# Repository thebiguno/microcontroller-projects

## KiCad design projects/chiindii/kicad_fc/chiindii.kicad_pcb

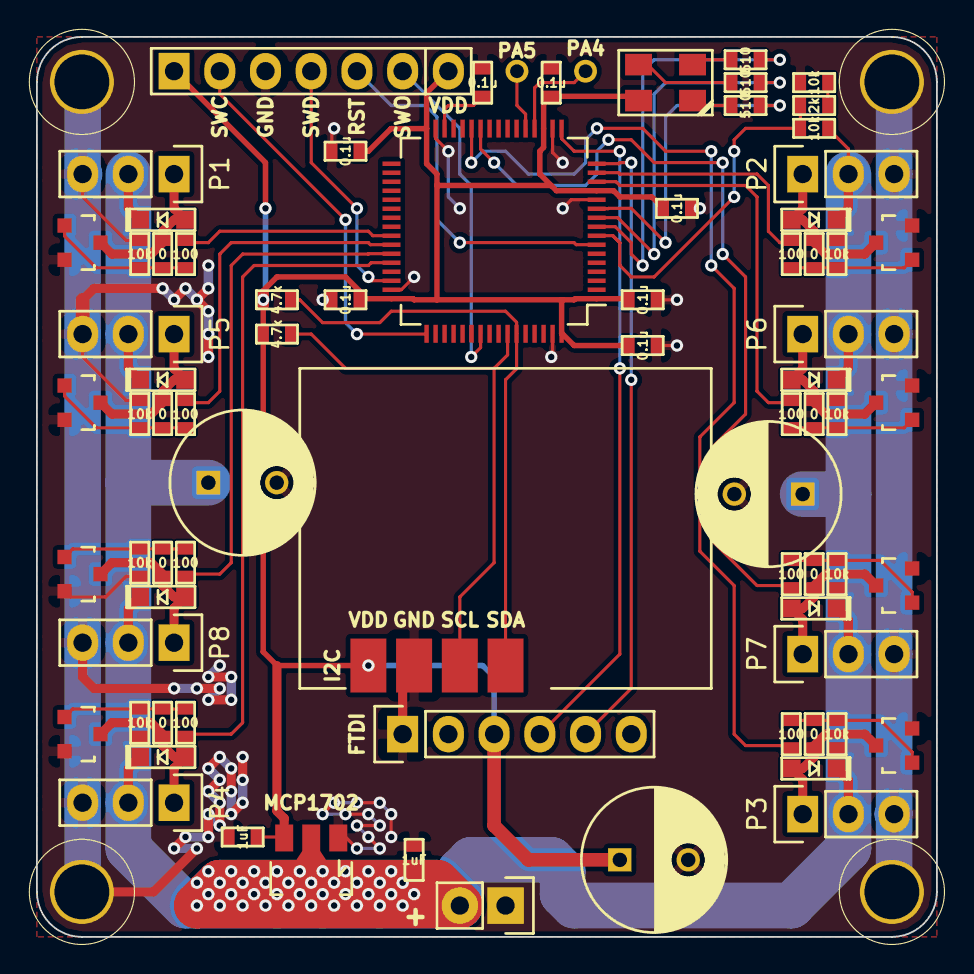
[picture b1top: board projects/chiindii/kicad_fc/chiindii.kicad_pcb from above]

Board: 2 copper layers, 50.0 x 50.0 mm, 81 parts (0 on the bottom side), 46 nets.

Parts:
C1, C2: 1uF; SM0603_VALUE
C3, C4, C11, C12, C13, C14, C15: 0.1u; SM0603_VALUE
C5, C6, C7: 470uF; C_Radial_D8_L13_P3.8
D1, D2, D3, D4, D5, D6, D7, D8: DSCHSMALL; SOD-323_DIODE
D10: RGB_LED_COMMON_ANODE_ALT1; LED_RGB_4-PLCC_ALT1
MP1, MP2, MP3, MP4: MOUNTING_HOLE; MOUNTING_HOLE_#4
P1, P2, P3, P4, P5, P6, P7, P8: CONN_01X03; Pin_Header_Straight_1x03
P9: STLINK; Pin_Header_Straight_1x07
P10: BATTERY; Pin_Header_Straight_1x02
P27: FTDI; Pin_Header_Straight_1x06
P33: I2C; Pin_Header_Straight_1x04
Q1, Q2, Q3, Q4, Q5, Q6, Q7, Q8: Q_NMOS_GSD; SOT-23
R1, R2, R7, R8, R13, R14, R34, R35: 100; SM0603_VALUE
R3, R6, R10, R12, R17, R18, R28, R33, R37, R39: 10k; SM0603_VALUE
R4, R5, R9, R11, R15, R32, R36, R38: 0; SM0603_VALUE
R16: 2k; SM0603_VALUE
R20, R21, R22: 510; SM0603_VALUE
R24, R27: 4.7k; SM0603_VALUE
U3: STM32F411; LQFP-64_10x10mm_Pitch0.5mm
VR1: MCP1702; SOT89-3_Housing
W1, W2: TEST_1P; Pin_Header_Straight_1x01

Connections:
+3V3: C2.1, C3.2, C5.1, C11.2, C12.2, C13.2, C14.2, C15.2, D10.1, P9.1, P9.7, P27.3, P33.1, R24.2, R27.2, U3.1, U3.13, U3.19, U3.32, U3.48, U3.64, VR1.3
+BATT: C1.1, C6.1, C7.1, D1.2, D2.2, D3.2, D4.2, D5.2, D6.2, D7.2, D8.2, P1.2, P2.2, P3.2, P4.2, P5.2, P6.2, P7.2, P8.2, P10.2, R18.2, VR1.2
/BATT_ADC: R16.2, R18.1, U3.8
/MOTOR1: R1.1, U3.41
/MOTOR2: R2.1, U3.15
/MOTOR3: R7.1, U3.27
/MOTOR4: R8.1, U3.44
/MOTOR5: R13.1, U3.42
/MOTOR6: R14.1, U3.14
/MOTOR7: R34.1, U3.26
/MOTOR8: R35.1, U3.43
/NRST: P9.5, U3.7
/PA4: U3.20, W2.1
/PA5: U3.21, W1.1
/RADIO_RX: P27.5, U3.16
/RADIO_TX: P27.4, U3.17
/SCL: P33.3, R24.1, U3.58
/SDA: P33.4, R27.1, U3.59
/SWCLK: P9.2, U3.49
/SWDIO: P9.4, U3.46
/SWO: P9.6, U3.55
GND: C1.2, C2.2, C3.1, C4.2, C5.2, C6.2, C7.2, C11.1, C12.1, C13.1, C14.1, C15.1, MP1.1, MP2.1, MP3.1, MP4.1, P1.3, P2.3, P3.3, P4.3, P5.3, P6.3, P7.3, P8.3, P9.3, P10.1, P27.1, P33.2, Q1.2, Q2.2, Q3.2, Q4.2, Q5.2, Q6.2, Q7.2, Q8.2, R3.1, R6.1, R10.1, R12.1, R17.1, R28.1, R33.1, R37.1, R39.1, U3.12, U3.18, U3.31, U3.47, U3.63, VR1.1
unnamed: C4.1, U3.30
unnamed: D1.1, P1.1, Q1.3, R4.2
unnamed: D2.1, P2.1, Q2.3, R5.2
unnamed: D3.1, P3.1, Q3.3, R9.2
unnamed: D4.1, P4.1, Q4.3, R11.2
unnamed: D5.1, P5.1, Q5.3, R15.2
unnamed: D6.1, P6.1, Q6.3, R32.2
unnamed: D7.1, P7.1, Q7.3, R36.2
unnamed: D8.1, P8.1, Q8.3, R38.2
unnamed: D10.2, R22.1
unnamed: D10.3, R21.1
unnamed: D10.4, R20.1
unnamed: Q1.1, R1.2, R3.2, R4.1
unnamed: Q2.1, R2.2, R5.1, R6.2
unnamed: Q3.1, R7.2, R9.1, R10.2
unnamed: Q4.1, R8.2, R11.1, R12.2
unnamed: Q5.1, R13.2, R15.1, R28.2
unnamed: Q6.1, R14.2, R32.1, R33.2
unnamed: Q7.1, R34.2, R36.1, R37.2
unnamed: Q8.1, R35.2, R38.1, R39.2
unnamed: R16.1, R17.2
unnamed: R20.2, U3.9
unnamed: R21.2, U3.10
unnamed: R22.2, U3.11

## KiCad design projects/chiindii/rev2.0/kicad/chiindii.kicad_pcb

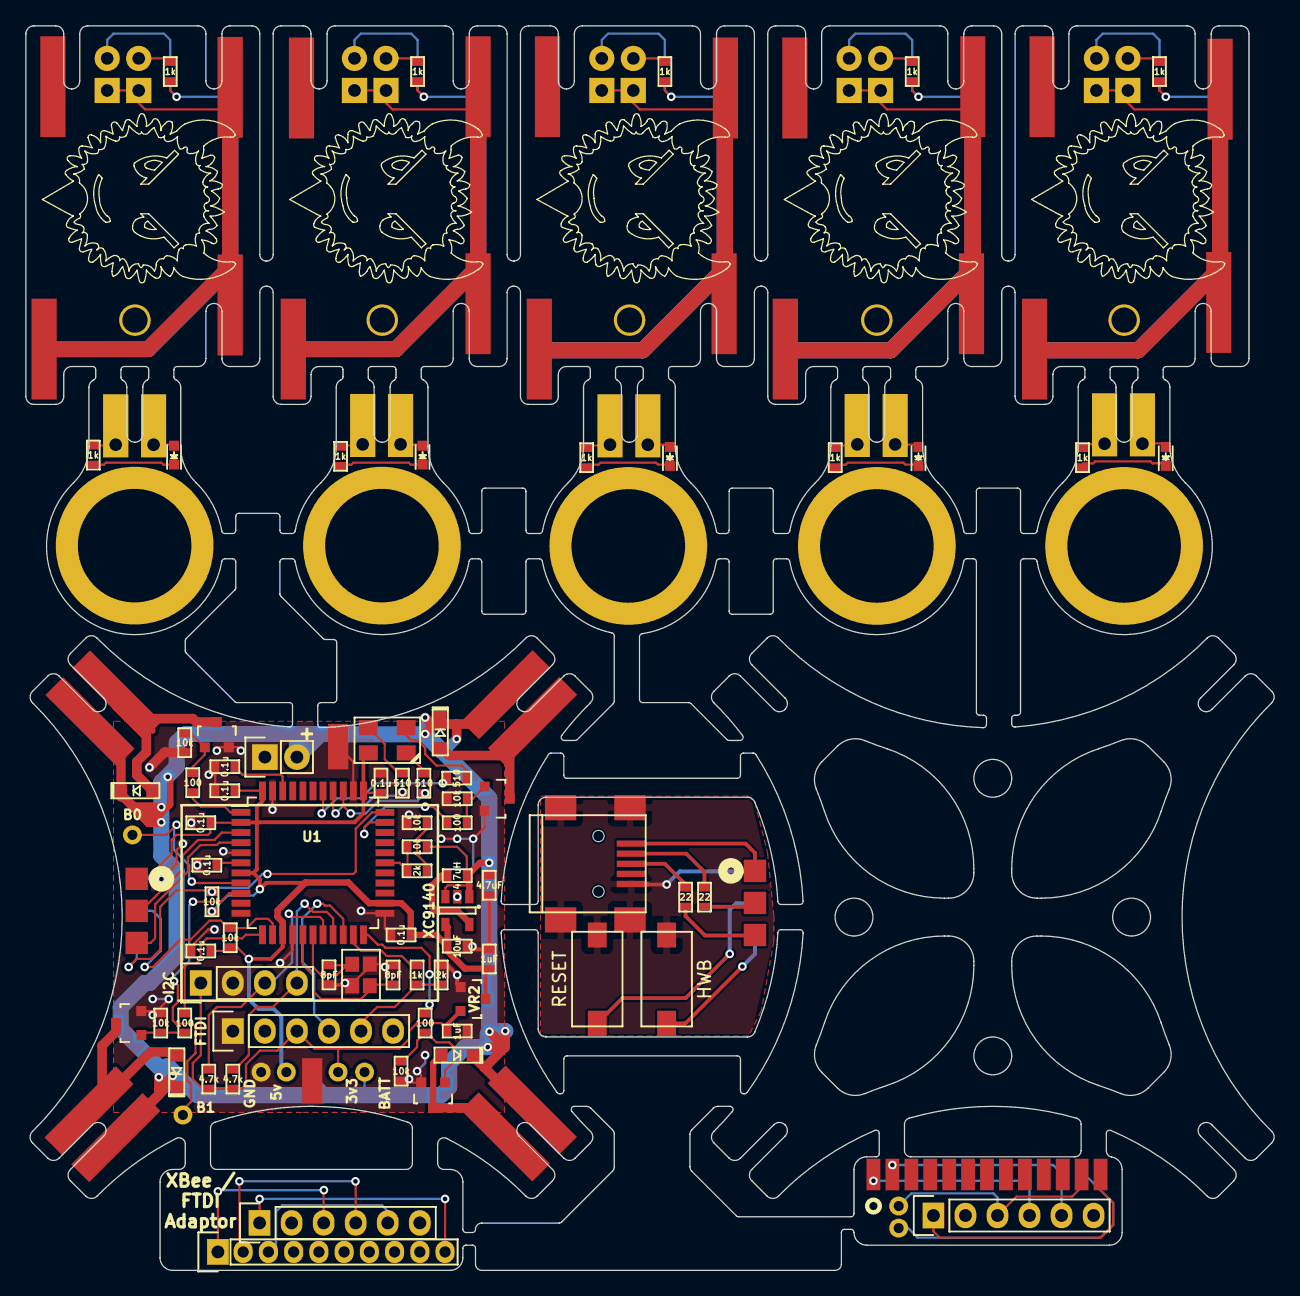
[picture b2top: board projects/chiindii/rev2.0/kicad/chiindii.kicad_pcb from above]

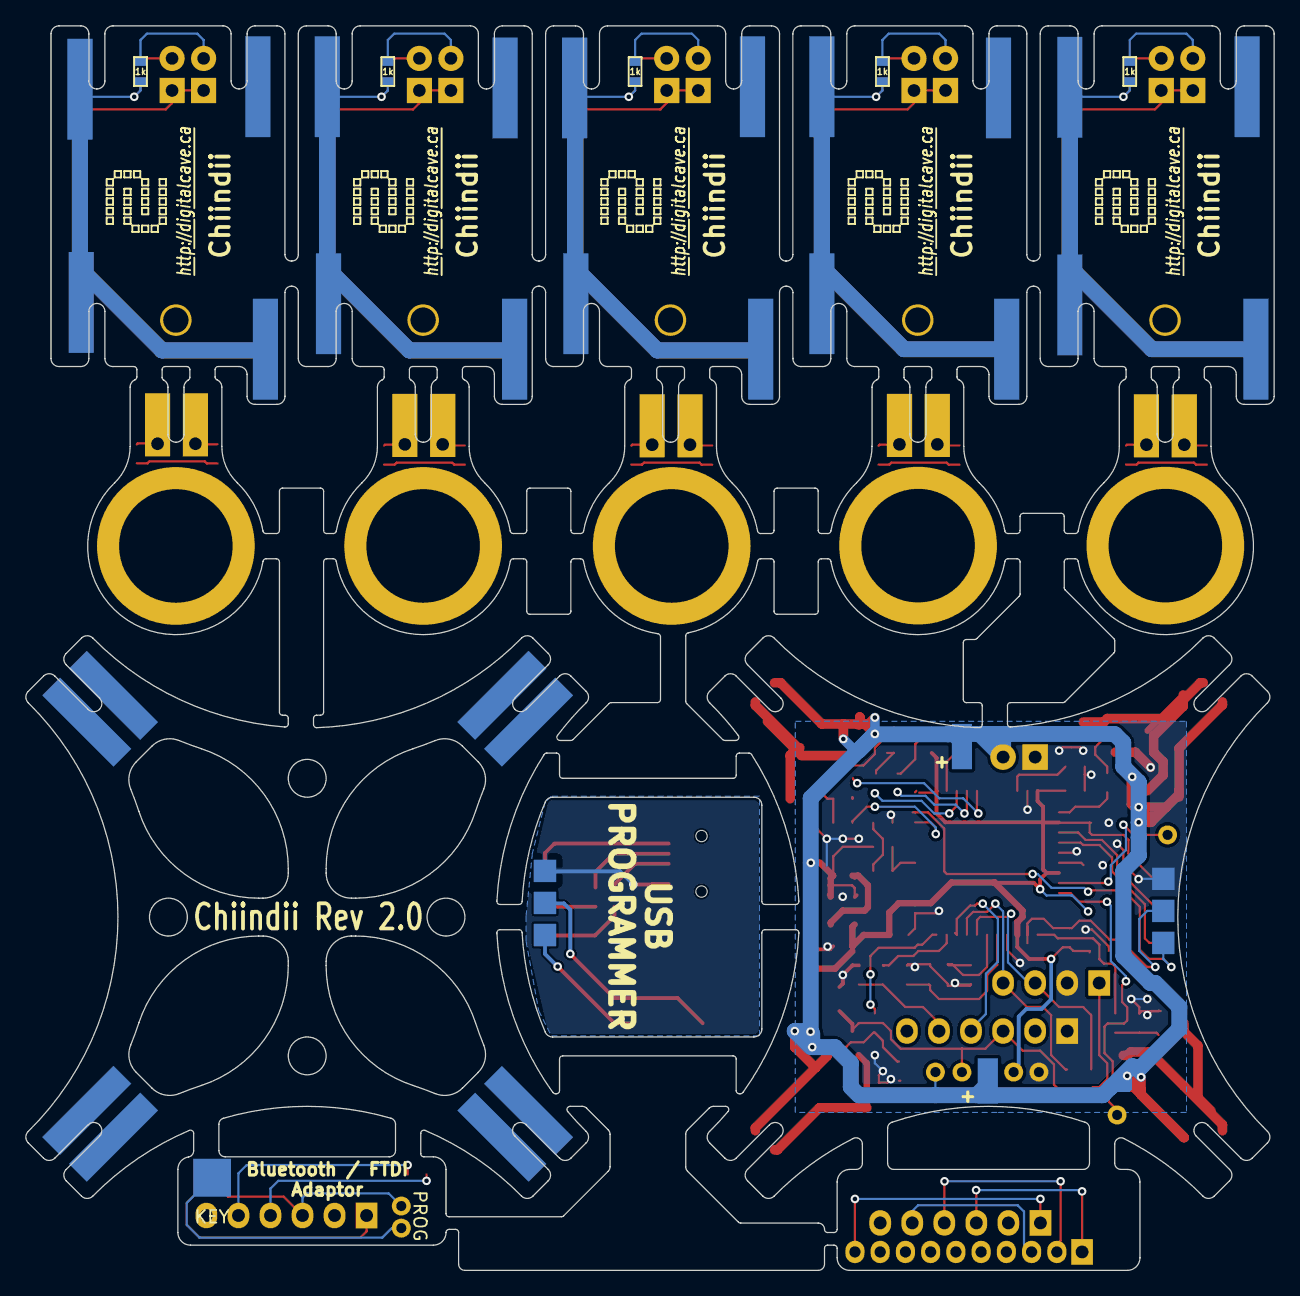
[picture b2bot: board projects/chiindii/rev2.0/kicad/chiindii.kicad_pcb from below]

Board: 2 copper layers, 98.9 x 98.6 mm, 154 parts (25 on the bottom side), 92 nets.

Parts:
C1, C2: 470uF; c_elec_6.3x5.8
C3: 4.7uF; SM0603_VALUE
C4: 10uF; SM0603_VALUE
C5, C6: 1uF; SM0603_VALUE
C7, C8: 8pF; SM0603_VALUE
C9, C10, C11, C12, C13, C14, C15: 0.1u; SM0603_VALUE
D1, D2, D3, D4: DSCHSMALL; SOD-323_DIODE
D5, D6, D7, D8, D9: LED; LED-0603
D10: RGB_LED_COMMON_ANODE_ALT1; LED_RGB_4-PLCC_ALT1
D11, D12, D13, D14, D15, D16, D17, D18, D19, D20: LED; LED-3MM
L1: 4.7uH; SM0603_VALUE
MP1, MP2, MP3, MP4, MP5: MOTOR; MOTOR_0820
MP6, MP9, MP12, MP15, MP18: GRAPHIC; DIGITALCAVE_LOGO
MP7, MP10, MP13, MP16, MP19: GRAPHIC; DIGITALCAVE_URL
MP8, MP11, MP14, MP17, MP20: HOLE; Pin_Header_Straight_1x01
P1: BATTERY; Pin_Header_Straight_1x02
P2: USB_OTG; USB_Mini-B
P3, P4, P6, P7: BODY_MOTOR_OUTPUT; H_JOINT
P5: PROG_CONN_A; ISP_EDGE
P8, P9, P10, P11, P12: V_MOTOR_IN; V_JOINT
P13, P14, P15, P16, P17, P18, P19, P20, P21, P22: V_MOTOR_OUT; V_JOINT
P23: 5v; Measurement_Point_Round-TH_Small
P24: 3v3; Measurement_Point_Round-TH_Small
P25: BATT; Measurement_Point_Round-TH_Small
P26: GND; Measurement_Point_Round-TH_Small
P27: FTDI; Pin_Header_Straight_1x06
P28, P29, P30, P31, P32: H_MOTOR_IN; H_JOINT_TH
P33: I2C; Pin_Header_Straight_1x04
P34, P35, P36, P37, P38: V_BAT_SUPPORT; V_JOINT
P39, P40, P41, P42: H_BAT_SUPPORT; H_JOINT
P43: PROG_CONN_B; ISP_EDGE
P44: XBEE_FTDI; Pin_Header_Straight_1x06
P45: XBEE; Pin_Header_Straight_1x10
P46: BT_FTDI; Pin_Header_Straight_1x06
P47: HC-05 / HM-10; Pin_Header_Straight_1x13
P48: PROG; Pin_Header_Straight_1x02
P49: KEY; Pin_Header_Straight_1x01
P50: B0; Measurement_Point_Round-TH_Small
P51: B1; Measurement_Point_Round-TH_Small
Q1, Q2, Q3, Q4: Q_NMOS_GSD; SOT-23
R1, R2, R7, R8: 100; SM0603_VALUE
R3, R4, R9, R10, R17, R18, R19, R25: 10k; SM0603_VALUE
R5, R6: 22; SM0603_VALUE
R11, R12, R13, R14, R15, R23, R28, R29, R30, R31, R32, R33, R34, R35, R36, R37: 1k; SM0603_VALUE
R16, R26: 2k; SM0603_VALUE
R20, R21, R22: 510; SM0603_VALUE
R24, R27: 4.7k; SM0603_VALUE
SW1: RESET; SW_6x3
SW2: HWB; SW_6x3
U1: ATMEGA32U4-A; TQFP-44_10x10mm_Pitch0.8mm
VR1: XC9140; SOT-23-5
VR2: MCP1702; SOT-23
X1: 16MHz; CRYSTAL_SMD_2.5x2

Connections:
+3V3: C6.1, P24.1, P27.3, P33.1, R24.2, R27.2, VR2.2
+5V: C4.1, C5.1, C11.2, C12.2, C13.2, C14.2, C15.2, D10.1, P23.1, P43.1, R19.2, R25.1, U1.2, U1.7, U1.14, U1.24, U1.34, U1.44, VR1.4, VR2.3
+BATT: C1.1, C2.1, C3.1, D1.2, D2.2, D3.2, D4.2, L1.1, P1.2, P3.1, P4.1, P6.1, P7.1, P25.1, R18.2, VR1.1, VR1.3
/B0: P50.1, U1.8
/B1: P51.1, U1.9
/BATT_ADC: R16.2, R18.1, U1.28
/D+: P43.5, U1.4
/D-: P43.3, U1.3
/DC+: P2.3, R5.1
/DC-: P2.2, R6.1
/DP+: P5.5, R5.2
/DP-: P5.3, R6.2
/HWB: P43.6, R25.2, U1.33
/MOTOR1: R1.1, U1.1
/MOTOR2: R2.1, U1.32
/MOTOR3: R7.1, U1.22
/MOTOR4: R8.1, U1.12
/PRG_GND: P2.5, P2.6, P5.2, SW1.1, SW2.1
/RADIO_RX: P27.5, R23.1, R26.2
/RADIO_TX: P27.4, U1.20
/RESET: P43.4, R19.1, U1.13
/SCL: P33.3, R24.1, U1.18
/SDA: P33.4, R27.1, U1.19
/X+: C7.1, U1.17, X1.1
/X-: C8.1, U1.16, X1.3
GND: C1.2, C2.2, C3.2, C4.2, C5.2, C6.2, C7.2, C8.2, C9.2, C10.2, C11.1, C12.1, C13.1, C14.1, C15.1, P1.1, P26.1, P27.1, P33.2, P43.2, Q1.2, Q2.2, Q3.2, Q4.2, R3.1, R4.1, R9.1, R10.1, R17.1, R26.1, U1.5, U1.15, U1.23, U1.35, U1.43, VR1.2, VR2.1, X1.2, X1.4
unnamed: C9.1, U1.6
unnamed: C10.1, U1.42
unnamed: D1.1, P3.2, Q1.3
unnamed: D2.1, P4.2, Q2.3
unnamed: D3.1, P6.2, Q3.3
unnamed: D4.1, P7.2, Q4.3
unnamed: D5.1, R11.2
unnamed: D5.2, P28.1
unnamed: D6.1, R12.2
unnamed: D6.2, P29.1
unnamed: D7.1, R13.2
unnamed: D7.2, P30.1
unnamed: D8.1, R14.2
unnamed: D8.2, P31.1
unnamed: D9.1, R15.2
unnamed: D9.2, P32.1
unnamed: D10.2, R22.1
unnamed: D10.3, R21.1
unnamed: D10.4, R20.1
unnamed: D11.1, D12.1, P8.2, P13.2, P18.2
unnamed: D11.2, R28.1
unnamed: D12.2, R29.1
unnamed: D13.1, D14.1, P9.2, P14.2, P19.2
unnamed: D13.2, R30.1
unnamed: D14.2, R31.1
unnamed: D15.1, D16.1, P10.2, P15.2, P20.2
unnamed: D15.2, R32.1
unnamed: D16.2, R33.1
unnamed: D17.1, D18.1, P11.2, P16.2, P21.2
unnamed: D17.2, R34.1
unnamed: D18.2, R35.1
unnamed: D19.1, D20.1, P12.2, P17.2, P22.2
unnamed: D19.2, R36.1
unnamed: D20.2, R37.1
unnamed: L1.2, VR1.5
unnamed: P2.1, P5.1
unnamed: P5.4, SW1.2
unnamed: P5.6, SW2.2
unnamed: P10.1, P15.1, P20.1, R32.2, R33.2
unnamed: P11.1, P16.1, P21.1, R34.2, R35.2
unnamed: P12.1, P17.1, P22.1, R36.2, R37.2
unnamed: P8.1, P13.1, P18.1, R28.2, R29.2
unnamed: P9.1, P14.1, P19.1, R30.2, R31.2
unnamed: P28.2, R11.1
unnamed: P29.2, R12.1
unnamed: P30.2, R13.1
unnamed: P31.2, R14.1
unnamed: P32.2, R15.1
unnamed: P44.1, P45.10
unnamed: P44.3, P45.1
unnamed: P44.4, P45.2
unnamed: P44.5, P45.3
unnamed: P46.1, P47.13
unnamed: P46.3, P47.12, P48.1
unnamed: P46.4, P47.1
unnamed: P46.5, P47.2
unnamed: P48.2, P49.1
unnamed: Q1.1, R1.2, R3.2
unnamed: Q2.1, R2.2, R4.2
unnamed: Q3.1, R7.2, R9.2
unnamed: Q4.1, R8.2, R10.2
unnamed: R16.1, R17.2
unnamed: R20.2, U1.38
unnamed: R21.2, U1.37
unnamed: R22.2, U1.36
unnamed: R23.2, U1.21

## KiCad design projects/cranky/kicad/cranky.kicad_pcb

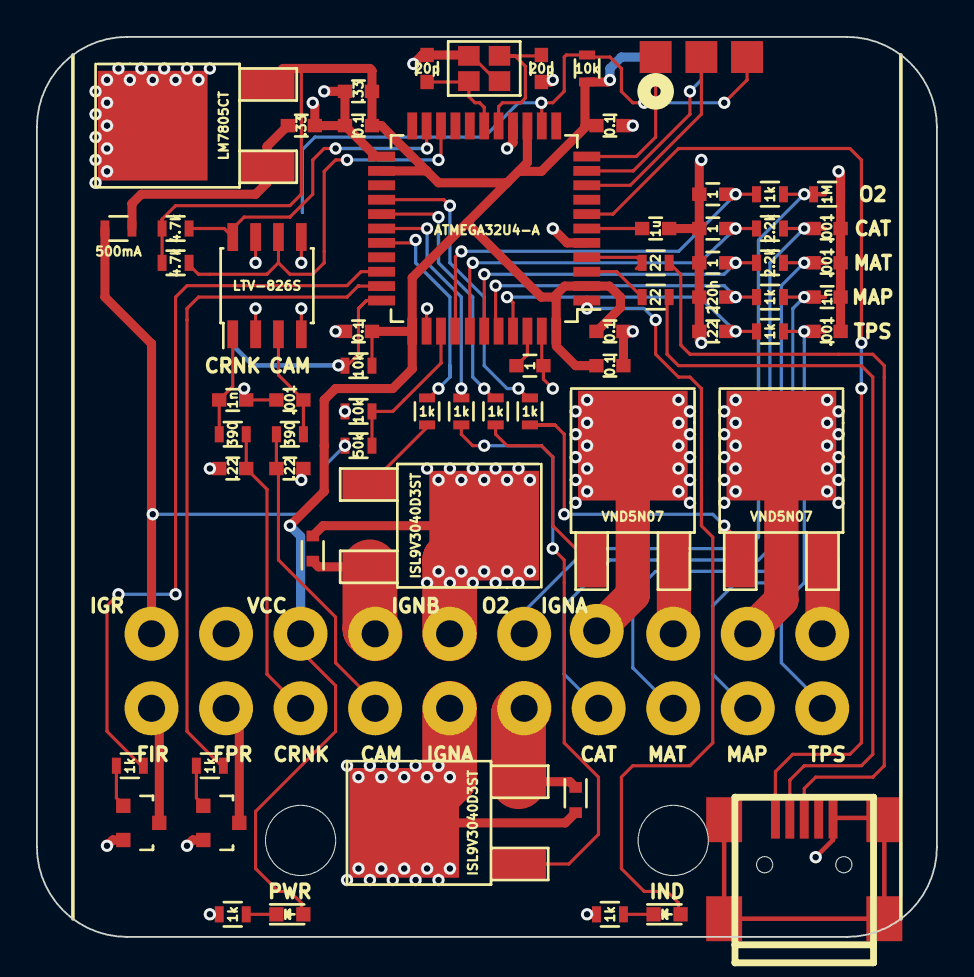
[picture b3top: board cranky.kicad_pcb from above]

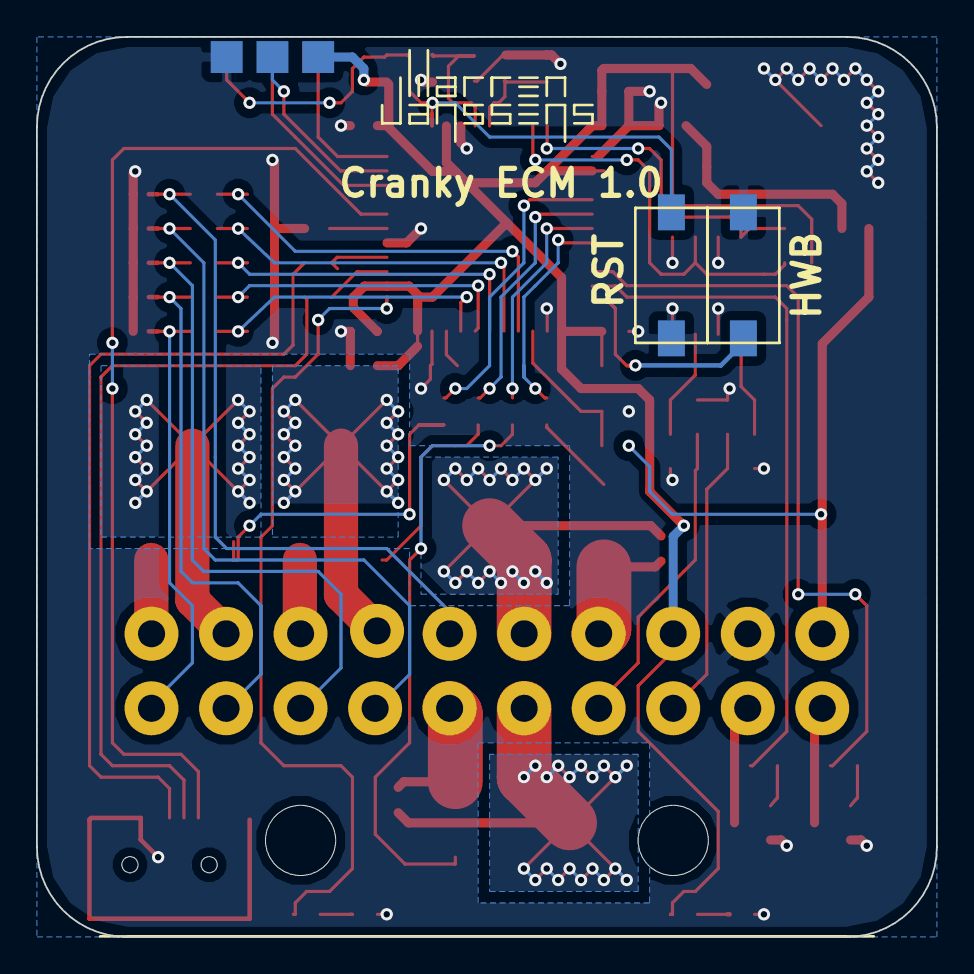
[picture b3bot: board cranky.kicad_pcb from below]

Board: 2 copper layers, 50.0 x 50.0 mm, 69 parts (4 on the bottom side), 60 nets.

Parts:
C1, C2, C6: .22; C_0603
C3, C5, C19, C20: .001; C_0603
C4, C18: 1n; C_0603
C7, C10: 20p; C_0603
C8: 1u; C_0603
C9, C11: .33; C_0603
C12, C13, C14, C15, C17: 0.1; C_0603
C16, C22, C23, C24: 1; C_0603
C21: 220n; C_0603
CON1: USB-MINI-B; USB_MINI_B_fixed
D1, D2: 1N4005; SOD-523
D3, D4: Led_Small; LED-0603
F1: 500mA; R_0603
P1: ISP; ISP_EDGE
P2: AMP794106
Q1, Q2: 2N7002P; SOT-23
Q3, Q4: ISL9V3040D3ST; TO-252-2Lead
Q5, Q6: VND5N07; TO-252-2Lead
R1, R2: 390; R_0603
R3, R7, R8, R10, R11, R12, R13, R18, R21, R23, R24: 1k; R_0603
R4, R9, R22: 10k; R_0603
R5, R6: 22; R_0603
R14, R15: 4.7k; R_0603
R16: 1M; R_0603
R17: 50k; R_0603
R19, R20: 2.2k; R_0603
SW1, SW2: SW_PUSH_SMALL; SW_6x3
U1: ATMEGA32U4-A; TQFP-44_10x10mm_Pitch0.8mm
U2: LTV-826S; SOIC-8_3.9x4.9mm_Pitch1.27mm
U3: LM7805CT; TO-252-2Lead
WJ20: VAL**; WJ20
X1: 16MHz; CRYSTAL_SMD_2.5x2

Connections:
//HWB: R9.2, SW2.1, U1.33
//RST: P1.5, R4.1, SW1.2, U1.13
/ADC0: C6.1, R3.1, U1.41
/ADC1: C21.1, R18.1, U1.40
/ADC4: C23.1, R20.1, U1.39
/ADC5: C22.1, R19.1, U1.38
/ADC6: C24.1, R21.1, U1.37
/ADC7: R17.1, R22.2, U1.36
/CAM: C2.1, P2.14, R2.2
/CAT: C19.1, P2.17, R19.2
/CRNK: C1.1, P2.13, R1.2
/D+: R5.2, U1.4
/D-: R6.2, U1.3
/FIR: P2.11, Q2.3
/FPR: P2.12, Q1.3
/IGNA: D1.2, P2.15, Q3.2
/IGNA_GND: D1.1, P2.16, Q3.3
/IGNB: D2.2, P2.5, Q4.2
/IGNB_GND: D2.1, P2.4, Q4.3
/IGR: F1.1, P2.1, R17.2
/INJA: P2.7, Q5.D
/INJA_GND: P2.8, Q5.S
/INJB: P2.9, Q6.D
/INJB_GND: P2.10, Q6.S
/INT2: R15.1, U1.20, U2.6
/INT3: R14.1, U1.21, U2.8
/LED: D4.2, U1.1
/MAP: C18.1, P2.19, R18.2
/MAT: C20.1, P2.18, R20.2
/MISO: P1.1, U1.11
/MOSI: P1.4, U1.10
/O2: P2.6, R16.1, R21.2
/PB4: R10.2, U1.28
/PB5: R11.2, U1.29
/PC6: R8.1, U1.31
/PC7: R7.1, U1.32
/PD6: R13.2, U1.26
/PD7: R12.2, U1.27
/SCLK: P1.3, U1.9
/TPS: C3.1, P2.20, R3.2
/UCAP: C8.1, U1.6
/UDM: CON1.2, R6.1
/UDP: CON1.3, R5.1
/VBUS: CON1.1, U1.7
/X+: C10.2, U1.17, X1.1
/X-: C7.2, U1.16, X1.3
DGND: C1.2, C2.2, C3.2, C4.2, C5.2, C6.2, C7.1, C8.2, C9.2, C10.1, C11.2, C12.1, C13.1, C14.1, C15.1, C16.2, C17.1, C18.2, C19.2, C20.2, C21.2, C22.2, C23.2, C24.2, CON1.5, CON1.6, CON1.7, CON1.8, CON1.9, P1.6, P2.2, Q1.2, Q2.2, R16.2, R22.1, R23.2, R24.1, SW1.1, SW2.2, U1.5, U1.15, U1.23, U1.35, U1.43, U2.2, U2.4, U2.5, U2.7, U3.2, X1.2, X1.4
unnamed: C4.1, R1.1, U2.1
unnamed: C5.1, R2.1, U2.3
unnamed: C9.1, F1.2, U3.1
unnamed: C16.1, U1.42
unnamed: D3.1, R23.1
unnamed: D4.1, R24.2
unnamed: Q1.1, R7.2
unnamed: Q2.1, R8.2
unnamed: Q3.1, R10.1
unnamed: Q4.1, R11.1
unnamed: Q5.G, R12.1
unnamed: Q6.G, R13.1
VCC: C11.1, C12.2, C13.2, C14.2, C15.2, C17.2, D3.2, P1.2, P2.3, R4.2, R9.1, R14.2, R15.2, U1.2, U1.14, U1.24, U1.34, U1.44, U3.3

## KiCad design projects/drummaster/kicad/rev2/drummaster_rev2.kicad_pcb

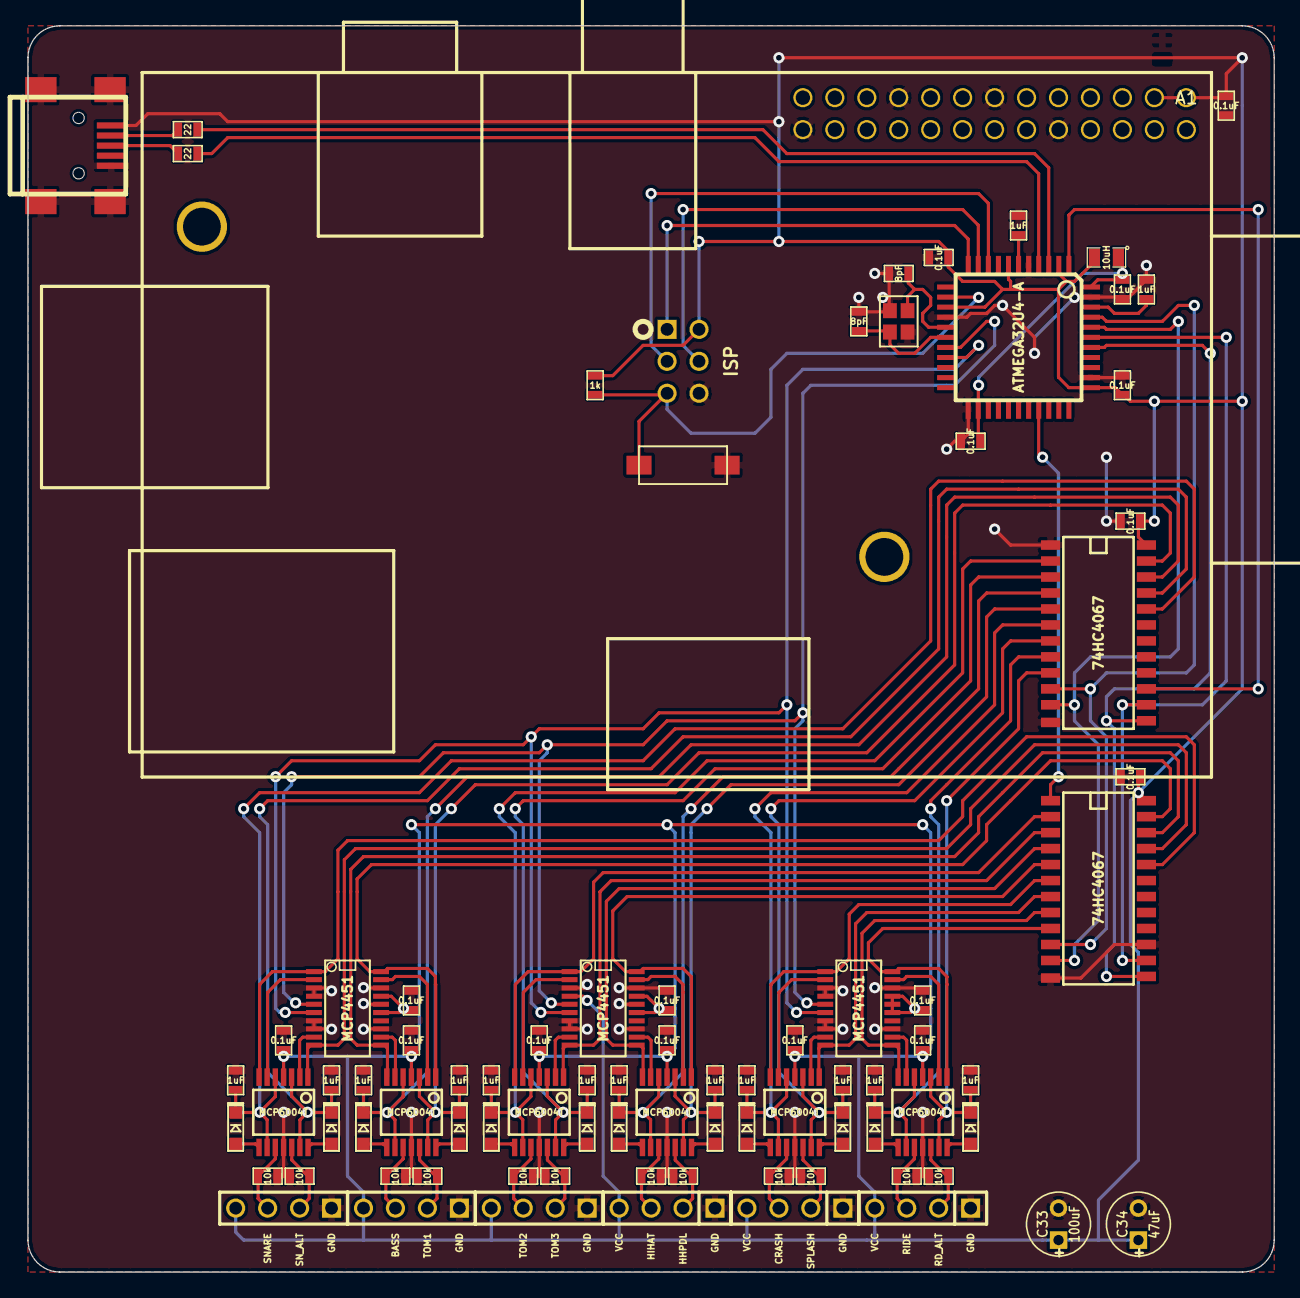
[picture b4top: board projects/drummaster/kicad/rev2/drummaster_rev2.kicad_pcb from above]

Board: 2 copper layers, 99.1 x 99.1 mm, 85 parts (0 on the bottom side), 83 nets.

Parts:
A1: RASPBERRY_PI_MODEL_B_REV2
C1, C2, C8, C9, C10, C11, C12, C17, C18, C22, C23, C24, C25, C26: 1uF; SM0603_VALUE
C3, C4, C5, C6, C7, C13, C14, C15, C16, C21, C27, C28, C29, C30, C31, C32: 0.1uF; SM0603_VALUE
C19, C20: 8pF; SM0603_VALUE
C33: 100uF; C1V5
C34: 47uF; C1V5
CON1: USB-MINI-B; USB_MINI_B_fixed
D1, D2, D3, D4, D5, D6, D7, D8, D9, D10, D11, D12: DIODESCH; SOD-323_DIODE
K1, K2, K3, K4, K5, K6: CONN_4; PIN_ARRAY_4x1
L1: 10uH; SM0805
P7: ISP
R1, R2, R3, R4, R5, R6, R7, R8, R9, R10, R11, R12: 10k; SM0603_VALUE
R13, R15: 22; SM0603_VALUE
R14: 1k; SM0603_VALUE
SW1: SW_PUSH_SMALL; SW_6x3
U1: ATMEGA32U4-A; TQFP44
U2, U3, U4, U5, U6, U7: MCP6004T; SSOP14
U8, U9, U10: MCP4451; SSOP20
U11, U12: 74HC4067; SOIC24
X1: CRYSTAL_SMD_4PIN; crystal_smd_2.5x2

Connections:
+5V: A1.2, A1.4, C3.1, C4.1, C5.1, C6.1, C7.1, C15.1, C16.1, C21.1, C27.1, C28.1, C29.1, C30.1, C31.1, C32.1, C33.1, C34.1, CON1.1, K1.4, K2.4, K3.4, K4.4, K5.4, K6.4, L1.2, P7.2, R14.1, U1.2, U1.7, U1.14, U1.34, U2.4, U3.4, U4.4, U5.4, U6.4, U7.4, U8.15, U8.17, U9.4, U9.15, U9.17, U10.15, U10.16, U10.17, U11.24, U12.24
+5VA: C13.2, C14.2, L1.1, U1.24, U1.44
/ADC_INPUT: U1.30, U12.1
/AREF: C18.1, U1.42
/DRAIN_ENABLE: U1.1, U11.15
/MISO: P7.1, U1.11
/MOSI: P7.4, U1.10
/MUX0: U1.41, U11.10, U12.10
/MUX1: U1.40, U11.11, U12.11
/MUX2: U1.39, U11.14, U12.14
/MUX3: U1.38, U11.13, U12.13
/RESET: P7.5, R14.2, SW1.1, U1.13
/SCL: U1.18, U8.5, U9.5, U10.5
/SCLK: P7.3, U1.9
/SDA: U1.19, U8.6, U9.6, U10.6
/UCAP: C17.1, U1.6
GND: A1.9, A1.14, A1.20, A1.25, C1.2, C2.2, C3.2, C4.2, C5.2, C6.2, C7.2, C8.2, C9.2, C10.2, C11.2, C12.2, C13.1, C14.1, C15.2, C16.2, C17.2, C18.2, C19.2, C20.2, C21.2, C22.2, C23.2, C24.2, C25.2, C26.2, C27.2, C28.2, C29.2, C30.2, C31.2, C32.2, C33.2, C34.2, CON1.5, CON1.6, CON1.7, CON1.8, CON1.9, K1.1, K2.1, K3.1, K4.1, K5.1, K6.1, P7.6, R1.2, R2.2, R3.2, R4.2, R5.2, R6.2, R7.2, R8.2, R9.2, R10.2, R11.2, R12.2, SW1.2, U1.5, U1.15, U1.23, U1.35, U1.43, U2.11, U3.11, U4.11, U5.11, U6.11, U7.11, U8.3, U8.4, U8.7, U8.8, U8.13, U8.16, U8.18, U9.3, U9.7, U9.8, U9.13, U9.16, U9.18, U10.3, U10.4, U10.7, U10.8, U10.13, U10.18, U11.1, U11.12, U12.12, U12.15, X1.2, X1.4
unnamed: U2.2, U8.9
unnamed: U3.2, U8.19
unnamed: U5.2, U9.19
unnamed: U4.1, U9.10, U12.3
unnamed: U4.2, U9.9
unnamed: U6.2, U10.9
unnamed: C23.1, D9.2, U6.5, U6.9, U11.6
unnamed: U6.6, U10.2
unnamed: C24.1, D10.2, U6.3, U6.13, U11.7
unnamed: D9.1, U6.8
unnamed: D10.1, U6.14
unnamed: U7.6, U10.12
unnamed: U7.2, U10.19
unnamed: C25.1, D11.2, U7.5, U7.9, U11.8
unnamed: C26.1, D12.2, U7.3, U7.13, U11.9
unnamed: D11.1, U7.8
unnamed: D12.1, U7.14
unnamed: U6.7, U10.1, U12.6
unnamed: U6.1, U10.10, U12.7
unnamed: U7.7, U10.11, U12.8
unnamed: U7.1, U10.20, U12.9
unnamed: K5.3, R9.1, U6.10
unnamed: K5.2, R10.1, U6.12
unnamed: K6.2, R12.1, U7.12
unnamed: K6.3, R11.1, U7.10
unnamed: C20.1, U1.16, X1.1
unnamed: C19.1, U1.17, X1.3
unnamed: CON1.2, R15.2
unnamed: CON1.3, R13.2
unnamed: R13.1, U1.4
unnamed: R15.1, U1.3
unnamed: U2.7, U8.1, U12.20
unnamed: U2.6, U8.2
unnamed: C2.1, D2.2, U2.3, U2.13, U11.21
unnamed: U2.1, U8.10, U12.21
unnamed: D1.1, U2.8
unnamed: C1.1, D1.2, U2.5, U2.9, U11.20
unnamed: D2.1, U2.14
unnamed: K1.2, R2.1, U2.12
unnamed: K1.3, R1.1, U2.10
unnamed: U4.6, U9.2
unnamed: C10.1, D5.2, U4.5, U4.9, U11.2
unnamed: K4.3, R7.1, U5.10
unnamed: C11.1, D6.2, U4.3, U4.13, U11.3
unnamed: D5.1, U4.8
unnamed: U4.7, U9.1, U12.2
unnamed: K3.2, R6.1, U4.12
unnamed: D6.1, U4.14
unnamed: C12.1, D7.2, U5.5, U5.9, U11.4
unnamed: U5.6, U9.12
unnamed: C22.1, D8.2, U5.3, U5.13, U11.5
unnamed: D7.1, U5.8
unnamed: U5.7, U9.11, U12.4
unnamed: U5.1, U9.20, U12.5
unnamed: K4.2, R8.1, U5.12
unnamed: D8.1, U5.14
unnamed: K2.2, R4.1, U3.12
unnamed: K2.3, R3.1, U3.10
unnamed: U3.6, U8.12
unnamed: C8.1, D3.2, U3.5, U3.9, U11.22
unnamed: K3.3, R5.1, U4.10
unnamed: C9.1, D4.2, U3.3, U3.13, U11.23
unnamed: D3.1, U3.8
unnamed: U3.7, U8.11, U12.22
unnamed: U3.1, U8.20, U12.23
unnamed: D4.1, U3.14
